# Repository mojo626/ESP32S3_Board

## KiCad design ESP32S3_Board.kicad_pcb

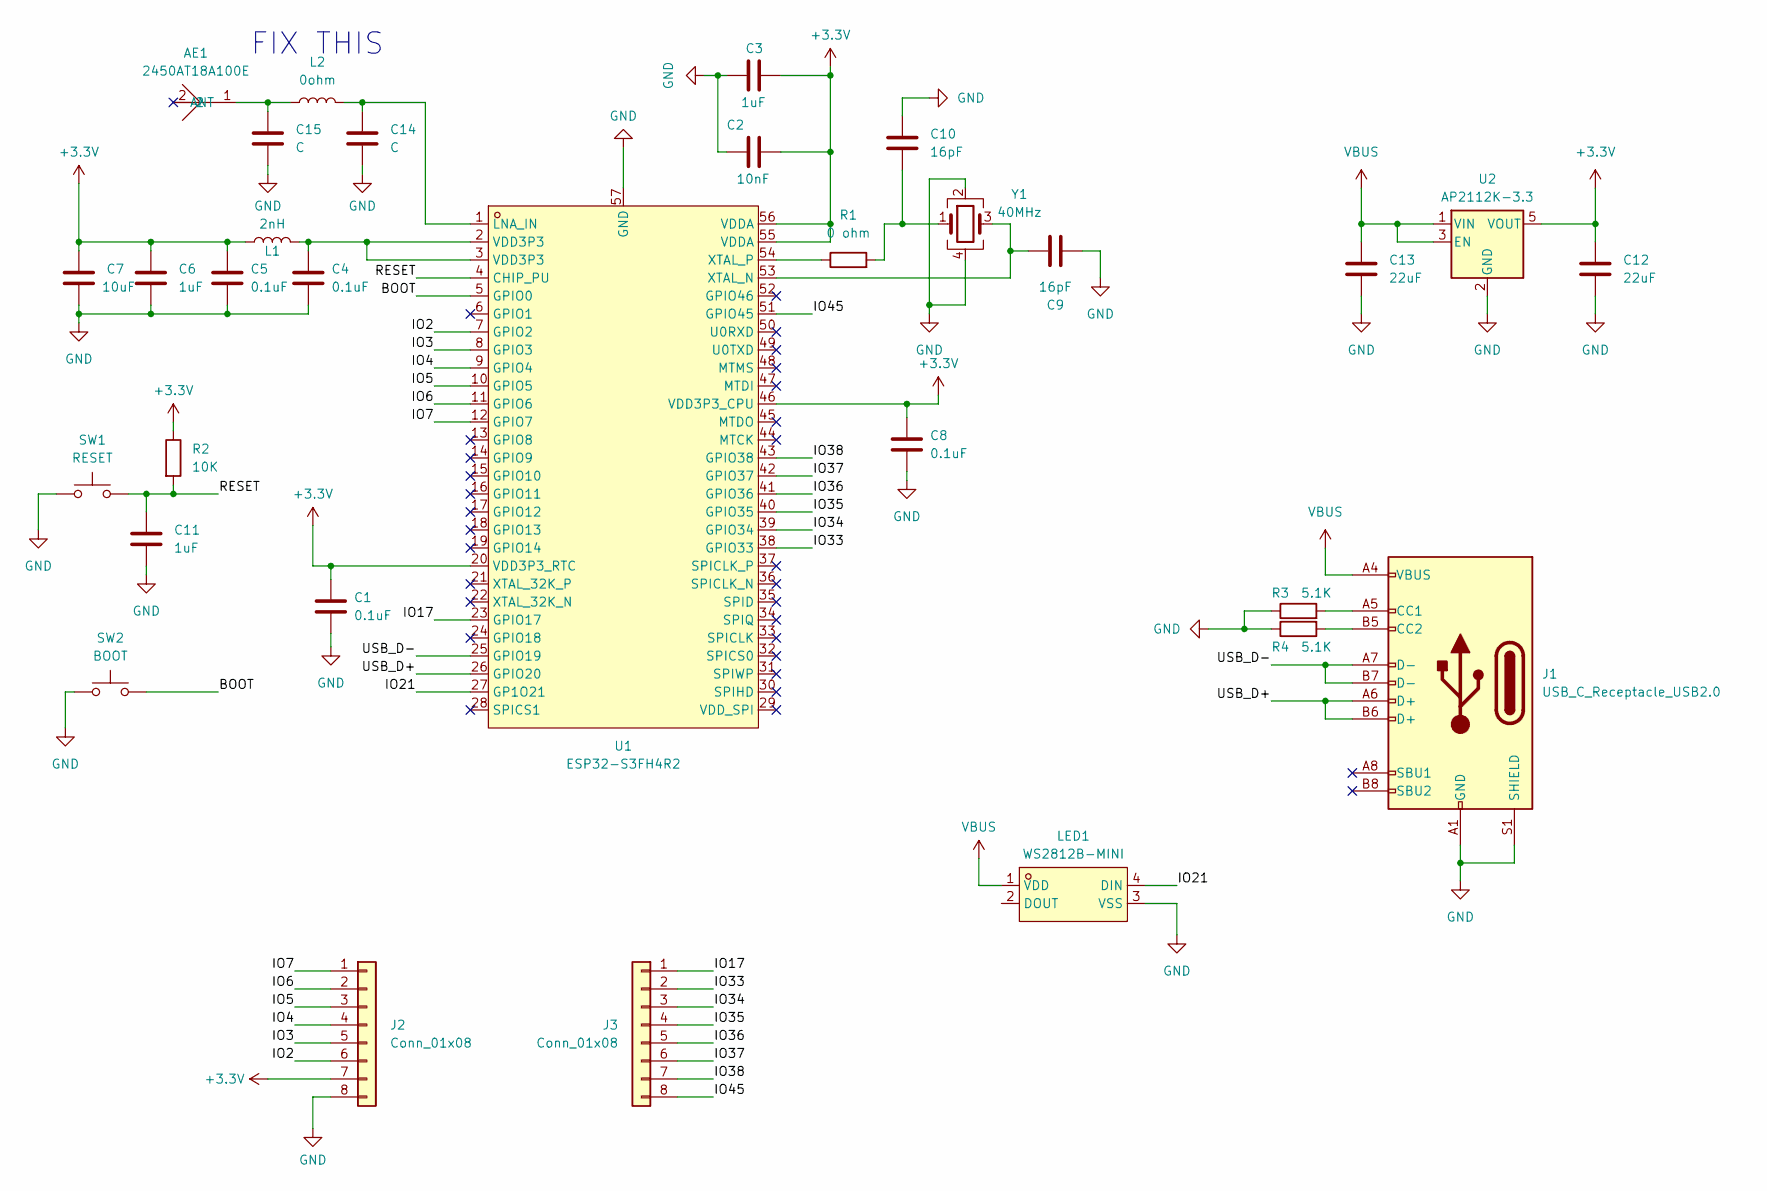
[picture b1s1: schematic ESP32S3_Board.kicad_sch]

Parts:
AE1: 2450AT18A100E; ANT-SMD_L3.2-W1.6; LCSC Part C89334
C1, C4, C5, C8: 0.1uF; C_0402_1005Metric
C2: 10nF; C_0402_1005Metric
C3, C6, C11: 1uF; C_0402_1005Metric
C7: 10uF; C_0603_1608Metric
C9, C10: 16pF; C_0402_1005Metric
C12, C13: 22uF; C_0805_2012Metric
C14, C15: C; C_0402_1005Metric
J1: USB_C_Receptacle_USB2.0; USB_C_Receptacle_HRO_TYPE-C-31-M-12
J2, J3: Conn_01x08; Castellated_8
L1: 2nH; L_0402_1005Metric
L2: 0ohm; L_0402_1005Metric
LED1: WS2812B-MINI; LED-SMD_4P-L3.5-W3.5-TL_WS2812B; LCSC Part C527089
R1: 0 ohm; R_0402_1005Metric
R2: 10K; R_0402_1005Metric
R3, R4: 5.1K; R_0402_1005Metric
SW1: RESET; SW-SMD_L3.1-W3.1-P2.20-LS4.0
SW2: BOOT; SW-SMD_L3.1-W3.1-P2.20-LS4.0
U1: ESP32-S3FH4R2; QFN-56_L7.0-W7.0-P0.40-TL-EP4.0; LCSC Part C3013940
U2: AP2112K-3.3; SOT-23-5
Y1: 40MHz; Crystal_SMD_3225-4Pin_3.2x2.5mm

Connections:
+3.3V: C1.1, C2.1, C3.1, C5.1, C6.1, C7.1, C8.1, C12.1, J2.7, L1.1, R2.1, U1.20 (VDD3P3_RTC), U1.46 (VDD3P3_CPU), U1.55 (VDDA), U1.56 (VDDA), U2.5 (VOUT)
/BOOT: SW2.2, U1.5 (GPIO0)
/IO2: J2.6, U1.7 (GPIO2)
/IO3: J2.5, U1.8 (GPIO3)
/IO4: J2.4, U1.9 (GPIO4)
/IO5: J2.3, U1.10 (GPIO5)
/IO6: J2.2, U1.11 (GPIO6)
/IO7: J2.1, U1.12 (GPIO7)
/IO17: J3.1, U1.23 (GPIO17)
/IO21: LED1.4 (DIN), U1.27 (GP1O21)
/IO33: J3.2, U1.38 (GPIO33)
/IO34: J3.3, U1.39 (GPIO34)
/IO35: J3.4, U1.40 (GPIO35)
/IO36: J3.5, U1.41 (GPIO36)
/IO37: J3.6, U1.42 (GPIO37)
/IO38: J3.7, U1.43 (GPIO38)
/IO45: J3.8, U1.51 (GPIO45)
/RESET: C11.1, R2.2, SW1.2, U1.4 (CHIP_PU)
/USB_D+: J1.A6 (D+), J1.B6 (D+), U1.26 (GPIO20)
/USB_D-: J1.A7 (D-), J1.B7 (D-), U1.25 (GPIO19)
GND: C1.2, C2.2, C3.2, C4.2, C5.2, C6.2, C7.2, C8.2, C9.2, C10.1, C11.2, C12.2, C13.2, C14.2, C15.2, J1.A1 (GND), J1.A12 (GND), J1.B1 (GND), J1.B12 (GND), J1.S1 (SHIELD), J2.8, LED1.3 (VSS), R3.1, R4.1, SW1.1, SW2.1, U1.57 (GND), U2.2 (GND), Y1.2, Y1.4
unnamed: AE1.1 (ANT), C15.1, L2.1
unnamed: C4.1, L1.2, U1.2 (VDD3P3), U1.3 (VDD3P3)
unnamed: C10.2, R1.2, Y1.1
unnamed: J1.A5 (CC1), R3.2
unnamed: J1.B5 (CC2), R4.2
unnamed: C14.1, L2.2, U1.1 (LNA_IN)
unnamed: C9.1, U1.53 (XTAL_N), Y1.3
unnamed: R1.1, U1.54 (XTAL_P)
VBUS: C13.1, J1.A4 (VBUS), J1.A9 (VBUS), J1.B4 (VBUS), J1.B9 (VBUS), LED1.1 (VDD), U2.1 (VIN), U2.3 (EN)

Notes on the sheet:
FIX THIS

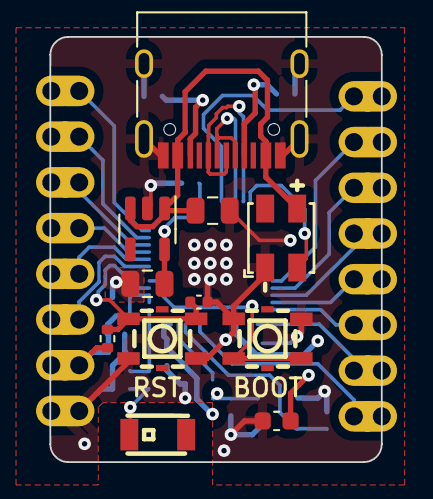
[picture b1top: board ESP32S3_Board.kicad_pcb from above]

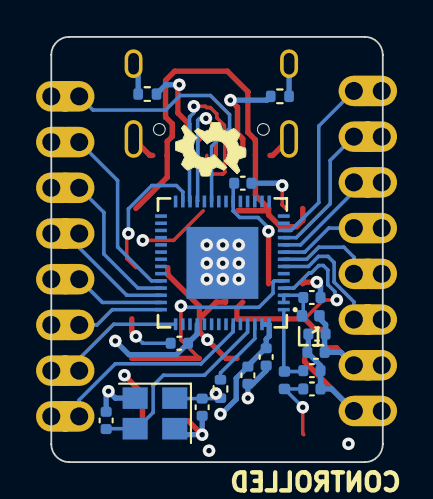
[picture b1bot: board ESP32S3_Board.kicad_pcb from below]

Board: 4 copper layers, 18.4 x 23.6 mm, 31 parts (18 on the bottom side), 30 nets.

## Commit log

2024-03-18 small changes
2024-03-18 manufacturing files
2024-03-18 manufacturing v2
